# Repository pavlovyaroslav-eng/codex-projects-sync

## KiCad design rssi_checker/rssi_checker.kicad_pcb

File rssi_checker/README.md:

# RSSI Checker — compact single-layer PCB

Main deliverable: `rssi_checker.kicad_pcb` (KiCad 9).

## Implemented constraints

- Board outline: **55.88 × 53.34 mm**.
- Routed copper: **F.Cu only**; GND zone is also on F.Cu.
- Main track width: **0.8 mm**; all corners are 45° or orthogonal.
- Short **0.3 mm neck-downs** exist only at the fine-pitch USB-C and ESP32 pads and in their immediate fan-out. A true 0.8 mm trace cannot enter the 0.65/1.27 mm pitch pads without a copper-clearance violation.
- Exactly two wire links: **JP1** for the 74HC4051 common output and **JP2** for KRL.
- U1 is **74HC4051N, DIP-16, socket footprint**; there are no CD4066 footprints.
- U2 is an **ESP32-WROOM-32 module**. Its antenna end is at the board edge and the antenna keep-out projects outside the board.
- C3 and C4 are **220 µF, 16 V, radial D8 mm / P3.5 mm** electrolytics.
- J8 is a right-angle, edge-mounted USB-C power receptacle. CC1 and CC2 each have a 5.1 kΩ pull-down.
- J1 is a right-angle two-pin banana/video-output connector.
- J2–J7 are right-angle 1×3 connectors in one row at the board edge. Their physical pad order is **Signal | +5V | GND**.

## 74HC4051 / ESP32 mapping

| Function | ESP32 GPIO | Module pad |
|---|---:|---:|
| MUX common Z | GPIO13 | 16 |
| Select S0/A | GPIO26 | 11 |
| Select S1/B | GPIO27 | 12 |
| Select S2/C | GPIO14 | 13 |
| Video output | GPIO25 | 10 |

| 4051 channel | Receiver | S2 S1 S0 |
|---|---|---|
| Y0 | KRL | 000 |
| Y1 | 2.4G | 001 |
| Y2 | TBS | 010 |
| Y3 | 915 | 011 |
| Y4 | 300 | 100 |
| Y5 | 500 | 101 |

U1 pin 16 is +3.3 V; pins 8 (GND), 7 (VEE), and 6 (/EN) are tied to GND. Therefore receiver signal inputs must stay within **0…3.3 V**.

## Before fabrication

Open the board in KiCad 9, press **B** to refill the GND zone, then run the native DRC and visually confirm the exact mechanical models of the purchased USB-C and banana connectors.

The supplied `rssi_checker.kicad_sch` is the untouched legacy CD4066 schematic from the archive and is retained only as a reference. It is **not synchronized** with this new 74HC4051 board; do not run “Update PCB from Schematic” against it.

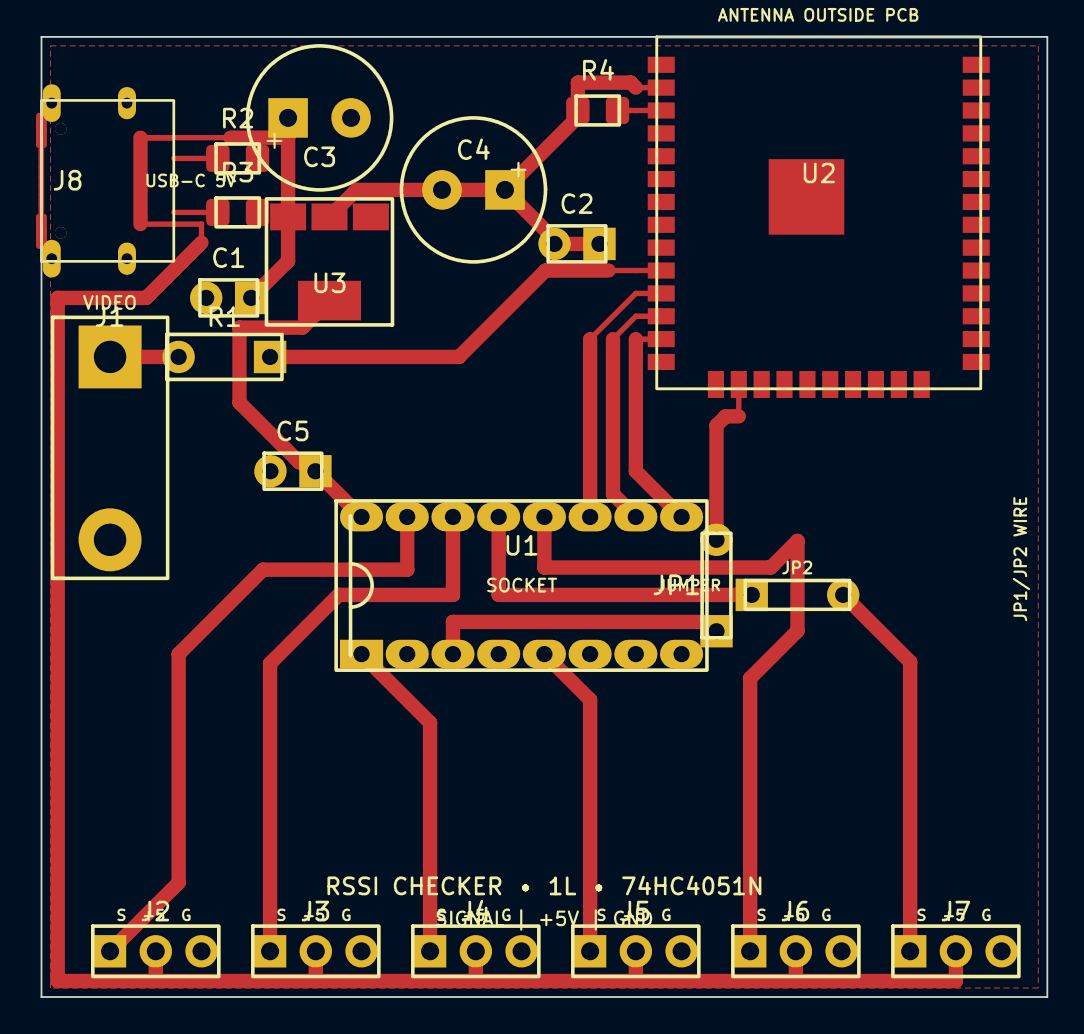
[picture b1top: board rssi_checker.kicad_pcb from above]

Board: 2 copper layers, 55.9 x 53.3 mm, 22 parts (0 on the bottom side), 20 nets.

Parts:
C1, C2, C5: 100n; C_Disc_D5.0mm_W2.5mm_P2.50mm
C3, C4: 220uF 16V; CP_Radial_D8.0mm_P3.50mm
J1: VIDEO_OUT_BANANA_RA; Banana_Jack_2Pin_P10.16mm_RightAngle
J2: TBS; PinHeader_1x03_P2.54mm_Horizontal
J3: 2.4G; PinHeader_1x03_P2.54mm_Horizontal
J4: 300; PinHeader_1x03_P2.54mm_Horizontal
J5: 500; PinHeader_1x03_P2.54mm_Horizontal
J6: 915; PinHeader_1x03_P2.54mm_Horizontal
J7: KRL; PinHeader_1x03_P2.54mm_Horizontal
J8: USB_C_POWER; USB_C_Receptacle_GCT_USB4105-xx-A_16P_TopMnt_Horizontal
JP1, JP2: WIRE_JUMPER; Wire_5.08mm
R1: 470R; R_Axial_DIN0207_L6.3mm_D2.5mm_P5.08mm_Horizontal
R2, R3: 5k1; R_0805_2012Metric_Pad1.20x1.40mm_HandSolder
R4: 10k EN; R_0805_2012Metric_Pad1.20x1.40mm_HandSolder
U1: 74HC4051N; DIP-16_W7.62mm_Socket_LongPads
U2: ESP32-WROOM-32
U3: LD1117S33TR; SOT-223-3_TabPin2

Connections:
+3V3: C2.1 (+), C4.1 (+), C5.1 (+), R4.1, U1.16 (VCC), U2.2, U3.2
+5V: C1.1 (+), C3.1 (+), J2.2 (+5V), J3.2 (+5V), J4.2 (+5V), J5.2 (+5V), J6.2 (+5V), J7.2 (+5V), J8.A4, J8.A9, J8.B4, J8.B9, U3.3
ESP_EN: R4.2, U2.3
GND: C1.2 (-), C2.2 (-), C3.2 (-), C4.2 (-), C5.2 (-), J1.2 (GND), J2.3 (GND), J3.3 (GND), J4.3 (GND), J5.3 (GND), J6.3 (GND), J7.3 (GND), J8.A1, J8.A12, J8.B1, J8.B12, J8.SH (Shield), R2.2, R3.2, U1.6 (~E), U1.7 (VEE), U1.8 (GND), U2.1, U2.15, U2.38, U2.39, U3.1
MUX_A0: U1.11 (S0), U2.11
MUX_A1: U1.10 (S1), U2.12
MUX_A2: U1.9 (S2), U2.13
MUX_Z: JP1.2, U1.3 (Z)
MUX_Z_JP: JP1.1, U2.16
RX_24: J3.1 (Signal), U1.14 (Y1)
RX_300: J4.1 (Signal), U1.1 (Y4)
RX_500: J5.1 (Signal), U1.5 (Y5)
RX_915: J6.1 (Signal), U1.12 (Y3)
RX_KRL_HDR: J7.1 (Signal), JP2.2
RX_KRL_MUX: JP2.1, U1.13 (Y0)
RX_TBS: J2.1 (Signal), U1.15 (Y2)
USB_CC1: J8.A5, R2.1
USB_CC2: J8.B5, R3.1
VIDEO: R1.1, U2.10
VIDEO_OUT: J1.1 (Signal), R1.2

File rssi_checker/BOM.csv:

Reference,Quantity,Value,Footprint,Notes
U1,1,74HC4051N,Package_DIP:DIP-16_W7.62mm_Socket_LongPads,DIP-16 socket required
U2,1,ESP32-WROOM-32,RF_Module:ESP32-WROOM-32,Module antenna at board edge
U3,1,LD1117S33TR,Package_TO_SOT_SMD:SOT-223-3_TabPin2,3.3 V regulator
C1 C2 C5,3,100n,Capacitor_THT:C_Disc_D5.0mm_W2.5mm_P2.50mm,Decoupling
C3 C4,2,220uF 16V,Capacitor_THT:CP_Radial_D8.0mm_P3.50mm,Electrolytic D8 P3.5
R1,1,470R,Resistor_THT:R_Axial_DIN0207_L6.3mm_D2.5mm_P5.08mm_Horizontal,Video output series resistor
R2 R3,2,5k1,Resistor_SMD:R_0805_2012Metric_Pad1.20x1.40mm_HandSolder,USB-C CC pull-down
R4,1,10k,Resistor_SMD:R_0805_2012Metric_Pad1.20x1.40mm_HandSolder,ESP32 EN pull-up
J1,1,VIDEO_OUT_BANANA_RA,Connector_Banana:Banana_Jack_2Pin_P10.16mm_RightAngle,Verify purchased connector pin pitch
J2-J7,6,Right-angle 1x3,Connector_PinHeader_2.54mm:PinHeader_1x03_P2.54mm_Horizontal,Signal +5V GND
J8,1,USB_C_POWER,Connector_USB:USB_C_Receptacle_GCT_USB4105-xx-A_16P_TopMnt_Horizontal,Power-only right-angle USB-C
JP1 JP2,2,WIRE_JUMPER,Jumper:Wire_5.08mm,Fit insulated wire links

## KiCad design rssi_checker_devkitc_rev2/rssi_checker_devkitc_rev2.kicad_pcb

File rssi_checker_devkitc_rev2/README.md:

# RSSI Checker — ESP32-DevKitC rev2

Эта ревизия переделана под фактическую плату с фотографий: **ESP32-DevKitC, 38 контактов (19×2)**, а не отдельный STM32 и не 30-контактный ESP32-модуль.

## Геометрия и монтаж

- Габарит несущей платы: **63,50 × 73,66 мм**, контур Г-образный.
- Посадочное место U2: **48,26 × 27,94 мм**, шаг контактов 2,54 мм, расстояние между рядами 25,40 мм.
- Micro-USB установленной DevKitC обращён к левому вырезу; антенна ESP32 — к правому краю.
- Под антенной исключена заливка GND.
- U1 — **74HC4051N DIP-16 в панельке**.
- Все обычные резисторы и неэлектролитические конденсаторы — **SMD 0805**.
- C3 и C4 — электролиты **220 мкФ, 16 В**, THT.
- J8 — угловой USB-C на правом краю.
- J1 — угловой банановый разъём на левом краю.
- J2…J7 стоят одним рядом у нижнего края; порядок каждого: **Signal | +5V | GND**.

## Трассировка

- Один медный слой: **F.Cu**.
- Основные дорожки: **0,8 мм**.
- Только локальный выход из мелкошаговых площадок USB-C, проход между его экранными лапами и короткий выход 3,3 В между контактами DevKitC: **0,3 мм**; далее питание расширяется до 0,8 мм.
- Все повороты — прямые или 45°.
- Ровно две изолированные проволочные перемычки: **JP1** (общий канал 4051) и **JP2** (сигнал 2.4G).
- Земля выполняется полигоном F.Cu. После открытия платы нажать **B**, затем запустить DRC.

## Назначение ESP32

- GPIO25 → общий вывод Z мультиплексора через JP1.
- GPIO14 → A0/S0.
- GPIO27 → A1/S1.
- GPIO26 → A2/S2.
- GPIO13 → VIDEO через R1 470 Ом на угловой банановый разъём.

Каналы 74HC4051:

| Код A2 A1 A0 | Канал | Разъём |
|---|---|---|
| 000 | Y0 | 500 |
| 001 | Y1 | 300 |
| 010 | Y2 | 2.4G |
| 011 | Y3 | 915 |
| 100 | Y4 | TBS |
| 101 | Y5 | KRL |

Y6 и Y7 не используются и посажены на GND; INH и VEE также на GND. U1 питается от 3,3 В DevKitC.

## Питание

USB-C используется только для питания +5 В; CC1 и CC2 имеют отдельные резисторы 5,1 кОм на GND. Не подавайте питание одновременно через USB-C этой платы и через Micro-USB/выводы питания DevKitC. Espressif разрешает три альтернативных способа питания DevKitC, но предупреждает использовать только один одновременно.

## Проверка

Автоматическая структурно-геометрическая проверка файла платы:

- баланс S-выражений: OK;
- 20 посадочных мест, 80 контактных площадок;
- только F.Cu;
- 0 пересечений между цепями;
- 0 нарушений дорожка–площадка;
- 0 нарушений площадка–площадка;
- 0 разрывов сигнальных/питающих цепей;
- 0 диагоналей, отличных от 45°;
- 2 перемычки.

Нативный KiCad DRC не запускался, потому что kicad-cli в среде отсутствует. Перед производством обязательно открыть проект в KiCad, заполнить полигон клавишей B, выполнить DRC и сверить конкретные артикулы USB-C, бананового и трёхконтактных угловых разъёмов с купленными деталями.

Официальная геометрия и распиновка:  
https://docs.espressif.com/projects/esp-dev-kits/en/latest/esp32/esp32-devkitc/user_guide.html  
https://dl.espressif.com/dl/schematics/esp32_devkitc_v4_dimensions.pdf

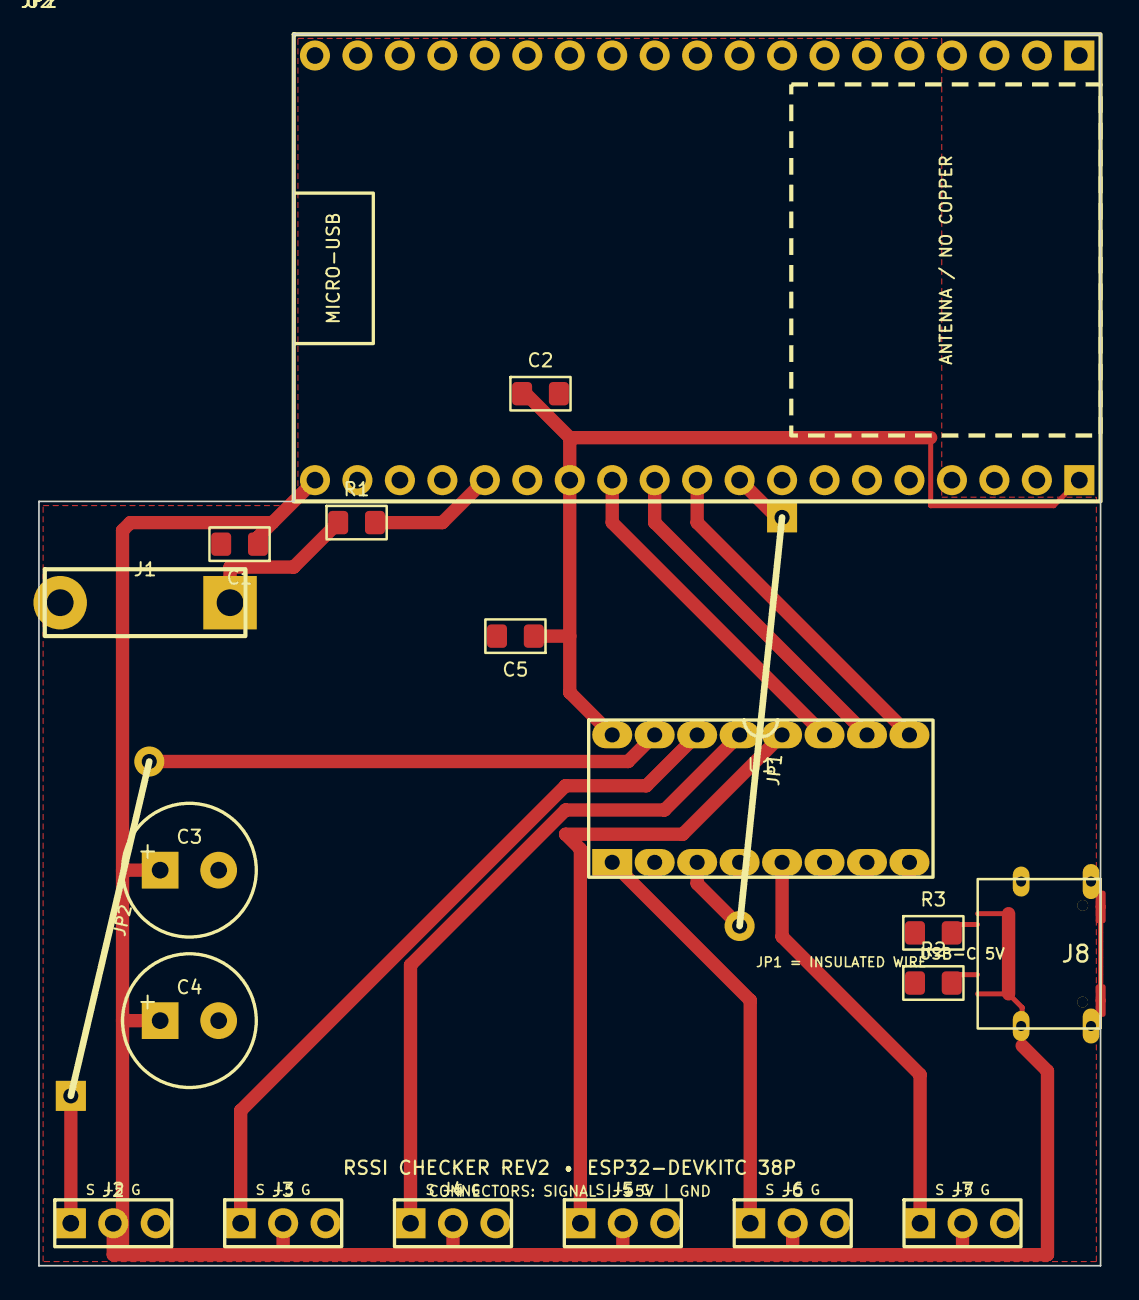
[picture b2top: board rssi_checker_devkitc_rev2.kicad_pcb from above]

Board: 2 copper layers, 63.5 x 73.7 mm, 20 parts (0 on the bottom side), 19 nets.

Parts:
C1, C2, C5: 100n; C_0805_2012Metric_Pad1.18x1.45mm_HandSolder
C3, C4: 220uF 16V; CP_Radial_D8.0mm_P3.50mm
J1: VIDEO_OUT_BANANA_RA; Banana_Jack_2Pin_P10.16mm_RightAngle
J2: 2.4G; PinHeader_1x03_P2.54mm_Horizontal
J3: 300; PinHeader_1x03_P2.54mm_Horizontal
J4: 500; PinHeader_1x03_P2.54mm_Horizontal
J5: 915; PinHeader_1x03_P2.54mm_Horizontal
J6: TBS; PinHeader_1x03_P2.54mm_Horizontal
J7: KRL; PinHeader_1x03_P2.54mm_Horizontal
J8: USB_C_POWER; USB_C_Receptacle_GCT_USB4105-xx-A_16P_TopMnt_Horizontal
JP1: INSULATED_WIRE; Wire_Custom_25mm
JP2: INSULATED_WIRE; Wire_Custom_20mm
R1: 470R; R_0805_2012Metric_Pad1.20x1.40mm_HandSolder
R2, R3: 5k1; R_0805_2012Metric_Pad1.20x1.40mm_HandSolder
U1: 74HC4051N; DIP-16_W7.62mm_Socket_LongPads
U2: ESP32-DevKitC_V4_38Pin; ESP32-DevKitC_V4_38Pin_Socket

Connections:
+3V3: C2.1, C5.1, U1.16, U2.J2-1
+5V: C1.1, C3.1 (+), C4.1 (+), J2.2 (+5V), J3.2 (+5V), J4.2 (+5V), J5.2 (+5V), J6.2 (+5V), J7.2 (+5V), J8.A4, J8.A9, J8.B4, J8.B9, U2.J2-19
GND: C1.2, C2.2, C3.2 (-), C4.2 (-), C5.2, J1.2 (GND), J2.3 (GND), J3.3 (GND), J4.3 (GND), J5.3 (GND), J6.3 (GND), J7.3 (GND), J8.A1, J8.A12, J8.B1, J8.B12, J8.SH (Shield), R2.1, R3.1, U1.2, U1.4, U1.6, U1.7, U1.8, U2.GND
MUX_A0: U1.11, U2.J2-12
MUX_A1: U1.10, U2.J2-11
MUX_A2: U1.9, U2.J2-10
MUX_Z: JP1.2, U1.3
MUX_Z_JP: JP1.1, U2.J2-9
RX_24: JP2.2, U1.15
RX_24_HDR: J2.1 (Signal), JP2.1
RX_300: J3.1 (Signal), U1.14
RX_500: J4.1 (Signal), U1.13
RX_915: J5.1 (Signal), U1.12
RX_KRL: J7.1 (Signal), U1.5
RX_TBS: J6.1 (Signal), U1.1
USB_CC1: J8.A5, R2.2
USB_CC2: J8.B5, R3.2
VIDEO: R1.2, U2.J2-15
VIDEO_OUT: J1.1 (Signal), R1.1

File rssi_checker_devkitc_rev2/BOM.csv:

Reference,Qty,Value,Package,Notes
U2,1,ESP32-DevKitC V4 38-pin,2x19 P2.54 row spacing 25.40 mm,Install in female headers; antenna at board edge
U1,1,74HC4051N,DIP-16,Install in DIP-16 socket
U1 socket,1,DIP-16 socket,DIP-16 7.62 mm,Required
R1,1,470R,0805,Video series resistor
R2 R3,2,5.1k,0805,USB-C CC pull-downs
C1 C2 C5,3,100nF,0805,Ceramic decoupling
C3 C4,2,220uF 16V,Radial D8 P3.5,Electrolytic
J1,1,VIDEO OUT,Banana jack 2-pin P10.16 right-angle,Verify purchased footprint
J2,1,2.4G,1x3 P2.54 right-angle,Signal +5V GND
J3,1,300,1x3 P2.54 right-angle,Signal +5V GND
J4,1,500,1x3 P2.54 right-angle,Signal +5V GND
J5,1,915,1x3 P2.54 right-angle,Signal +5V GND
J6,1,TBS,1x3 P2.54 right-angle,Signal +5V GND
J7,1,KRL,1x3 P2.54 right-angle,Signal +5V GND
J8,1,USB-C power,GCT USB4105 horizontal,USB 2.0 power only
JP1 JP2,2,Insulated wire,0.9 mm drilled pads,Fit after soldering
